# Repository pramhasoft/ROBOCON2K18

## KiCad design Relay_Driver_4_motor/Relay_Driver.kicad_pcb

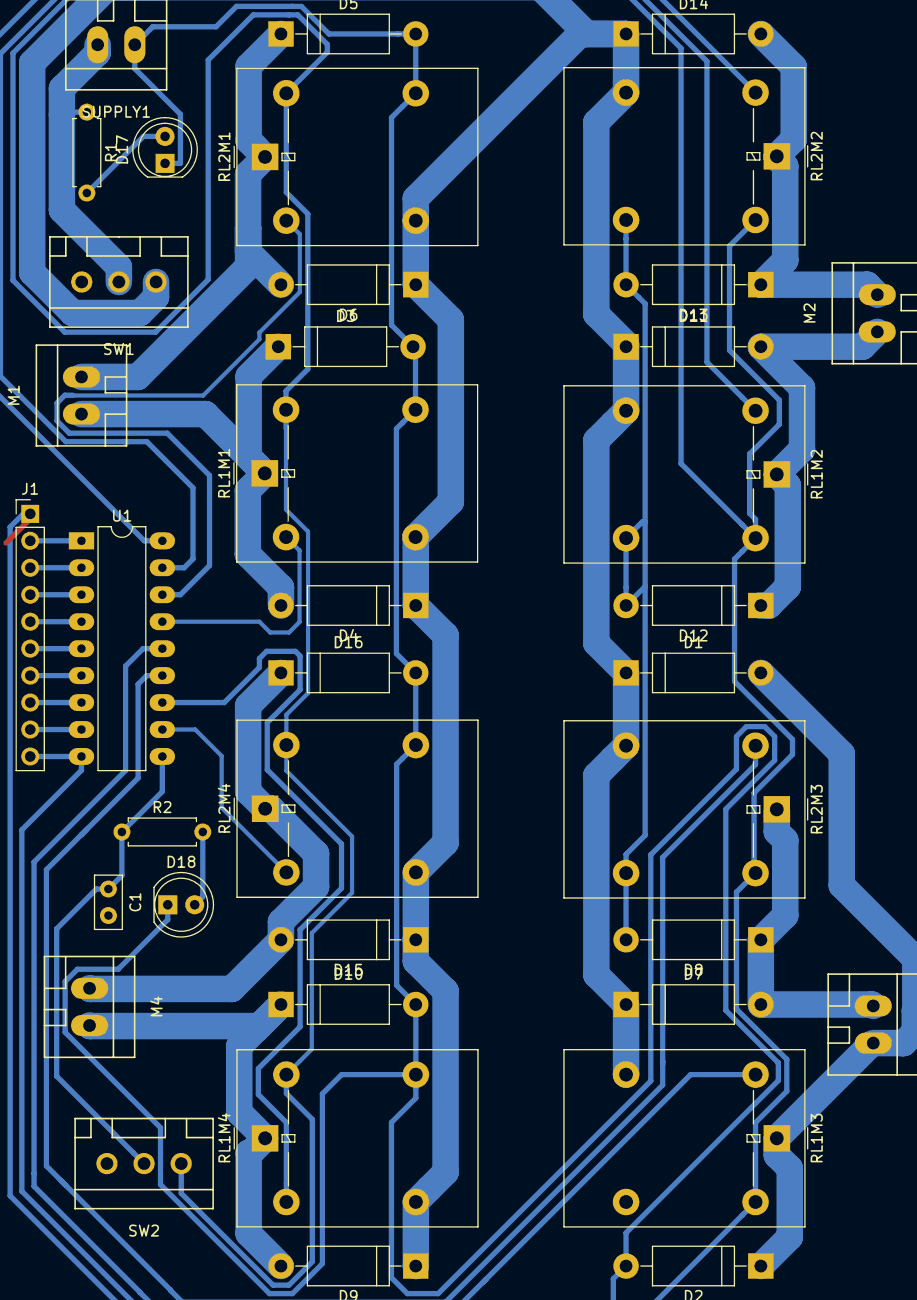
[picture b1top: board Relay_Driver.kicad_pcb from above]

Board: 2 copper layers, 38 parts (0 on the bottom side), 31 nets.

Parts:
C1: C; C_Disc_D5.0mm_W2.5mm_P2.50mm
D1, D2, D3, D4, D5, D6, D7, D8, D9, D10, D11, D12, D13, D14, D15, D16: D; D_DO-15_P12.70mm_Horizontal
D17, D18: LED; LED_D5.0mm_FlatTop
J1: Conn_01x10; Pin_Header_Straight_1x10_Pitch2.54mm
M1, M2, M3, M4: Conn_01x02; WAGO_734_2pin_Straight_RuggedPads
R1, R2: R_Small; R_Axial_DIN0207_L6.3mm_D2.5mm_P7.62mm_Horizontal
RL1M1, RL1M2, RL1M3, RL1M4, RL2M1, RL2M2, RL2M3, RL2M4: G5Q-1; Relay_SPDT_OMRON-G5LE-1
SUPPLY1: Conn_01x02; WAGO_734_2pin_Straight_RuggedPads
SW1, SW2: SW_SPDT; WAGO_734_3pin_Straight
U1: ULN2803A; DIP-18_W7.62mm_LongPads

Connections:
+5V: J1.1, RL1M1.5, RL1M2.5, RL1M3.5, RL1M4.5, RL2M1.5, RL2M2.5, RL2M3.5, RL2M4.5, SW2.1
+12V: D1.1, D4.1, D6.1, D7.1, D9.1, D11.1, D14.1, D15.1, RL1M1.3, RL1M2.3, RL1M3.3, RL1M4.3, RL2M1.3, RL2M2.3, RL2M3.3, RL2M4.3, SW1.1
GND: C1.2, D2.2, D3.2, D5.2, D8.2, D10.2, D12.2, D13.2, D16.2, D17.1, D18.1, J1.10, RL1M1.4, RL1M2.4, RL1M3.4, RL1M4.4, RL2M1.4, RL2M2.4, RL2M3.4, RL2M4.4, SUPPLY1.1, U1.9
unnamed: C1.1, R2.1, SW2.2, U1.10
unnamed: D1.2, D2.1, M3.2, RL1M3.2
unnamed: D3.1, D4.2, M1.1, RL1M1.2
unnamed: D5.1, D6.2, M1.2, RL2M1.2
unnamed: D7.2, D8.1, M3.1, RL2M3.2
unnamed: D9.2, D10.1, M4.2, RL1M4.2
unnamed: D11.2, D12.1, M2.1, RL1M2.2
unnamed: D13.1, D14.2, M2.2, RL2M2.2
unnamed: D15.2, D16.1, M4.1, RL2M4.2
unnamed: D17.2, R1.2
unnamed: D18.2, R2.2
unnamed: J1.2, U1.1
unnamed: J1.3, U1.2
unnamed: J1.4, U1.3
unnamed: J1.5, U1.4
unnamed: J1.6, U1.5
unnamed: J1.7, U1.6
unnamed: J1.8, U1.7
unnamed: J1.9, U1.8
unnamed: R1.1, SUPPLY1.2, SW1.2
unnamed: RL1M1.1, U1.15
unnamed: RL1M2.1, U1.17
unnamed: RL1M3.1, U1.14
unnamed: RL1M4.1, U1.12
unnamed: RL2M1.1, U1.16
unnamed: RL2M2.1, U1.18
unnamed: RL2M3.1, U1.13
unnamed: RL2M4.1, U1.11

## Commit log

2017-12-22 completed routing
